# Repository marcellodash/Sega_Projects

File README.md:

# Sega Megadrive_Projects
My Personnal projects for Sega Megadrive

DF_Audio : UART MP3 Player for Sega Megadrive

X-Flash : X-Flash is my Open-Souce alternative to Everdrive

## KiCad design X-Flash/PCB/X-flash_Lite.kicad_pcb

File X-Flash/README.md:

<<<<<<< HEAD
#X-flash

X-Flash is my open-source alternative to Everdrive
**Not finished Yet**
=======
# X-Flash an open source alternative to Everdrive

*Work in Progress*
>>>>>>> 893696249dab5398a9288cfb02d374caec2ab10a

Hardware folder : VHDL file for X-flash CPLD

PCB folder : Kicad + Gerber for the X-flash PCB

Software folder : source code and tools for the BIOS ROM

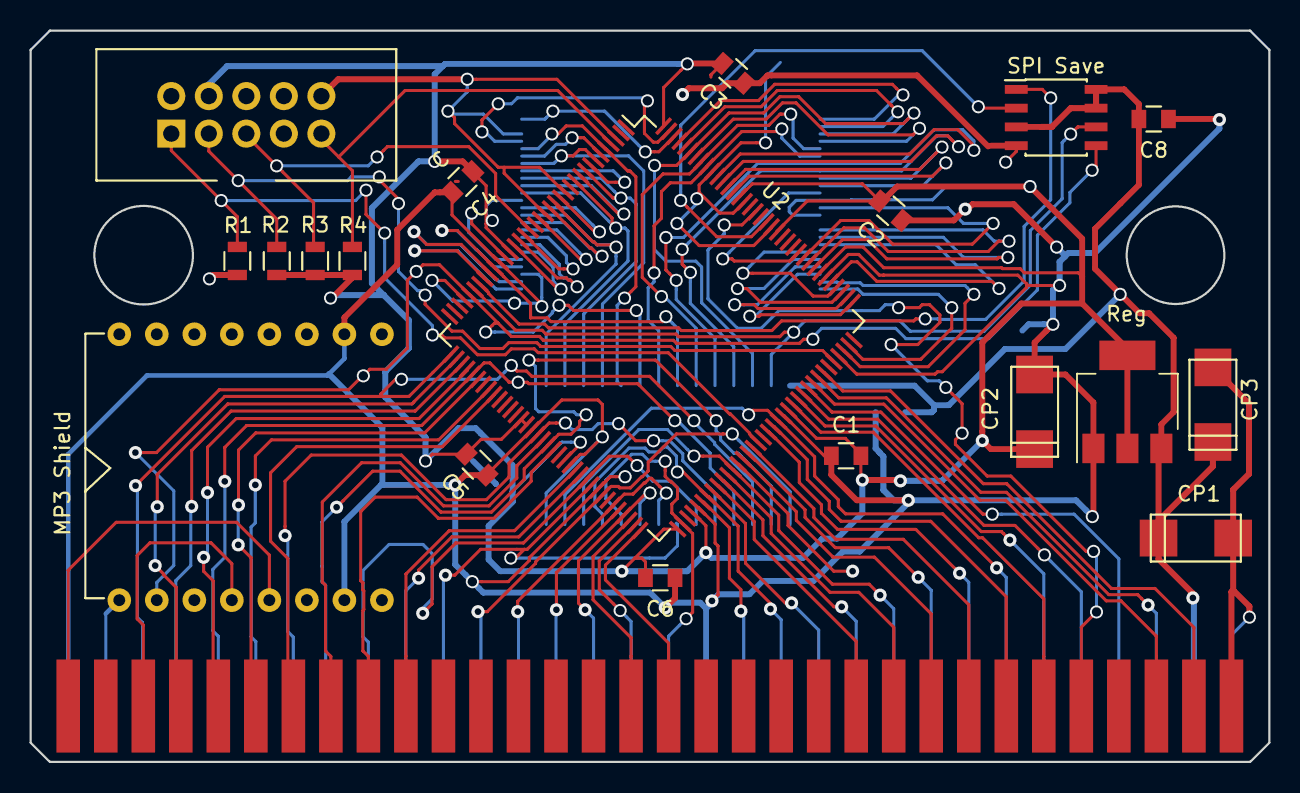
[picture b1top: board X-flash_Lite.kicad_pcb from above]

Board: 2 copper layers, 83.8 x 49.5 mm, 21 parts (0 on the bottom side), 52 nets.

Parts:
C1, C7: C_0805
C2, C3, C4, C5, C6, C8: C; C_0805
CP1: CP1; TantalC_SizeU_EIA-6032
CP2: CP2; TantalC_SizeU_EIA-6032
CP3: CP3; TantalC_SizeU_EIA-6032
J1: 0; AVR-JTAG-ICE
MP3 Shield: DIP-16_W7.62mm
R1, R2, R3, R4: 10K; R_0805
Reg: LM1117-3.3; SOT-223
SPI Save: 25AA512; SOIC-8_3.9x4.9mm_Pitch1.27mm
SST38VF6401: 0; M29W320D
U2: EPM3128ATC144; TQFP-144_20x20mm_Pitch0.5mm

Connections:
/FA0: SST38VF6401.25, U2.29
/FA1: SST38VF6401.24, U2.107
/FA2: SST38VF6401.23, U2.106
/FA3: SST38VF6401.22, U2.109
/FA4: SST38VF6401.21, U2.110
/FA5: SST38VF6401.20, U2.111
/FA6: SST38VF6401.19, U2.112
/FA7: SST38VF6401.18, U2.113
/FA8: SST38VF6401.8, U2.133
/FA9: SST38VF6401.7, U2.134
/FA10: SST38VF6401.6, U2.136
/FA11: SST38VF6401.5, U2.137
/FA12: SST38VF6401.4, U2.138
/FA13: SST38VF6401.3, U2.139
/FA14: SST38VF6401.2, U2.140
/FA15: SST38VF6401.1, U2.141
/FA16: SST38VF6401.48, U2.142
/FA17: SST38VF6401.17, U2.116
/FA18: SST38VF6401.16, U2.117
/FA19: SST38VF6401.9, U2.132
/FA20: SST38VF6401.10, U2.131
/FA21: SST38VF6401.13, U2.118
/FCE: SST38VF6401.26, U2.28
/FD0: SST38VF6401.29, U2.25
/FD1: SST38VF6401.31, U2.22
/FD2: SST38VF6401.33, U2.18
/FD3: SST38VF6401.35, U2.15
/FD4: SST38VF6401.38, U2.11
/FD5: SST38VF6401.40, U2.9
/FD6: SST38VF6401.42, U2.7
/FD7: SST38VF6401.44, U2.5
/FD8: SST38VF6401.30, U2.23
/FD9: SST38VF6401.32, U2.21
/FD10: SST38VF6401.34, U2.16
/FD11: SST38VF6401.36, U2.14
/FD12: SST38VF6401.39, U2.10
/FD13: SST38VF6401.41, U2.8
/FD14: SST38VF6401.43, U2.6
/FD15: SST38VF6401.45, U2.143
/FOE: SST38VF6401.28, U2.27
/FWE: SST38VF6401.11, U2.119
GND: C1.1, C2.1, C3.1, C4.2, C5.1, C6.1, C7.1, C8.1, CP1.2, CP2.2, CP3.2, J1.2, J1.10, MP3 Shield.7, MP3 Shield.10, R1.2, Reg.1, SPI Save.4, SST38VF6401.27, SST38VF6401.46, U2.3, U2.13, U2.17, U2.26, U2.33, U2.52, U2.59, U2.64, U2.77, U2.85, U2.94, U2.105, U2.114, U2.124, U2.129, U2.135
MISO: SPI Save.2, U2.125
MOSI/RX: MP3 Shield.2, SPI Save.5, U2.32
SCLK: SPI Save.6, U2.31
TCK: J1.1, R1.1, U2.89
TDI: J1.9, R4.1, U2.4
TDO: J1.3, R2.1, U2.104
TMS: J1.5, R3.1, U2.20
VCC3: C1.2, C2.2, C3.2, C4.1, C5.2, C6.2, CP2.1, J1.4, R2.2, R3.2, R4.2, Reg.2, Reg.4, SST38VF6401.12, SST38VF6401.14, SST38VF6401.37, U2.24, U2.50, U2.51, U2.58, U2.73, U2.76, U2.95, U2.115, U2.123, U2.130, U2.144
VCC5: C7.2, C8.2, CP1.1, CP3.1, MP3 Shield.1, Reg.3, SPI Save.3, SPI Save.7, SPI Save.8
~CE_SPI: SPI Save.1, U2.30

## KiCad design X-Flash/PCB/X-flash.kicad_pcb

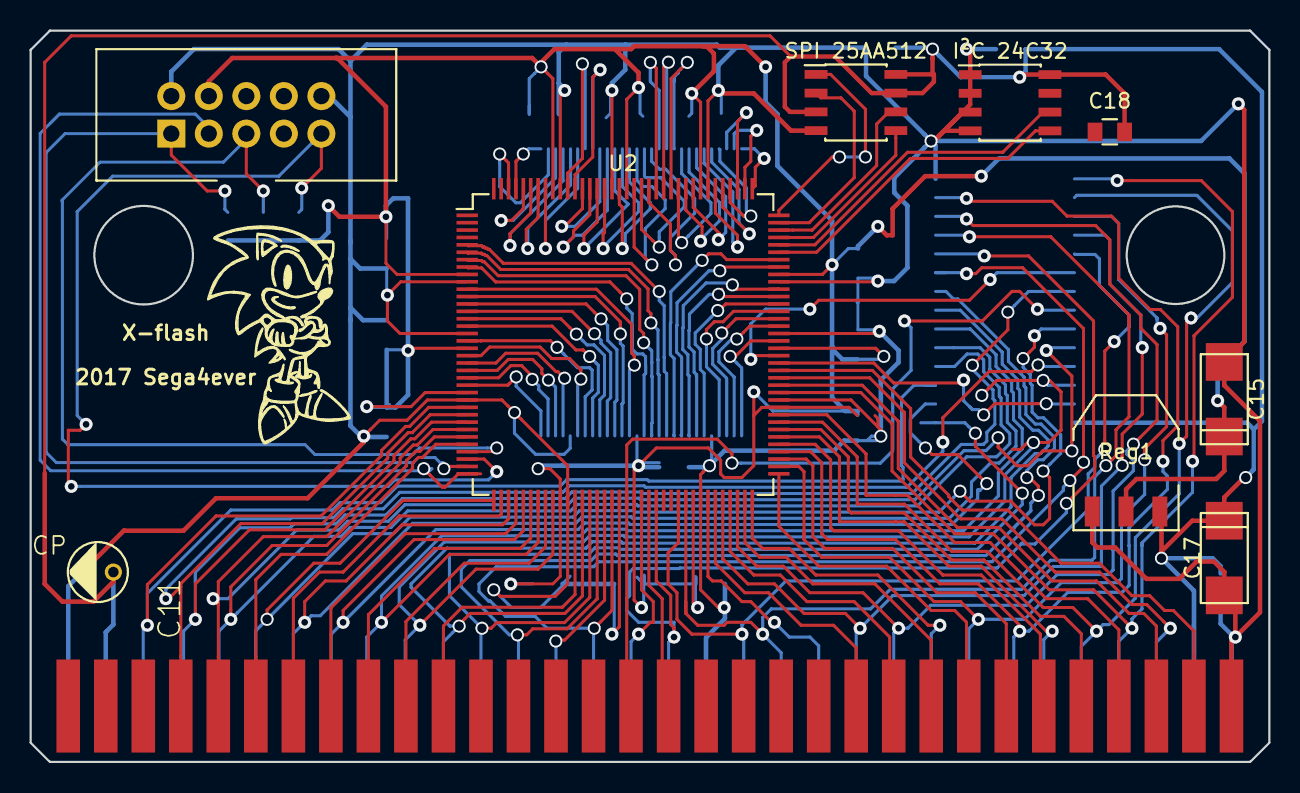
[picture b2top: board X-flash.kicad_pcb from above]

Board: 2 copper layers, 83.8 x 49.5 mm, 28 parts (0 on the bottom side), 62 nets.

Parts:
C1, C2, C3, C4, C5, C6, C7, C8, C9, C10, C12, C13, C14, C16, C18, C19, C20: C; C_0805
C11: CP; E1,8-4
C15, C17: CP; TantalC_SizeU_EIA-6032
IC1: FM1808B-SG; SOIC-28W_7.5x17.9mm_Pitch1.27mm
I²C 24C32: 24C32; SOIC-8_3.9x4.9mm_Pitch1.27mm
J1: 0; AVR-JTAG-ICE
P1: Sega
P2: 0; Sega
Reg1: SOT-223
SPI 25AA512: 25AA512; SOIC-8_3.9x4.9mm_Pitch1.27mm
U2: TQFP-144_20x20mm_Pitch0.5mm

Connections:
/A0: IC1.10, P2.17, U2.59
/A1: IC1.9, P2.15, U2.53
/A2: IC1.8, P2.13, U2.51
/A3: IC1.7, P2.11, U2.49
/A4: IC1.6, P2.9, U2.43
/A5: IC1.5, P2.7, U2.39
/A6: IC1.4, P2.5, U2.31
/A7: IC1.3, P2.3, U2.27
/A8: IC1.25, P1.4, U2.28
/A9: IC1.24, P1.5, U2.30
/A10: IC1.21, P2.4, U2.29
/A11: IC1.23, P2.6, U2.37
/A12: IC1.2, P2.8, U2.41
/A13: IC1.26, P2.10, U2.45
/A14: IC1.1, P2.12, U2.50
/A15: P2.14, U2.52
/A16: P2.16, U2.57
/A17: P1.6, U2.32
/A18: P1.7, U2.38
/A19: P1.8, U2.40
/A20: P1.9, U2.42
/A21: P1.10, U2.44
/A22: P1.11, U2.48
/CE: P1.17, U2.58
/D0: IC1.11, P2.20, U2.63
/D1: IC1.12, P2.23, U2.70
/D2: IC1.13, P2.26, U2.76
/D3: IC1.15, P2.29, U2.84
/D4: IC1.16, P2.28, U2.80
/D5: IC1.17, P2.25, U2.74
/D6: IC1.18, P2.22, U2.68
/D7: IC1.19, P2.19, U2.62
/D8: P2.21, U2.66
/D9: P2.24, U2.72
/D10: P2.27, U2.78
/D11: P2.30, U2.86
/D12: P1.25, U2.73
/D13: P1.24, U2.71
/D14: P1.23, U2.69
/D15: P1.22, U2.67
/OE: IC1.22, P1.16, U2.55
GND: C1.1, C2.2, C3.1, C4.2, C5.2, C6.2, C7.1, C8.1, C9.2, C10.2, C11.-, C12.2, C13.1, C14.2, C15.2, C16.2, C17.2, C19.2, C20.1, IC1.14, I²C 24C32.1, I²C 24C32.2, I²C 24C32.3, I²C 24C32.4, J1.2, J1.10, P1.32, P2.1, P2.18, P2.32, Reg1.1, SPI 25AA512.4, U2.10, U2.17, U2.26, U2.47, U2.54, U2.65, U2.83, U2.92, U2.99, U2.115, U2.128, U2.135
MISO: SPI 25AA512.2, U2.107
MOSI: SPI 25AA512.5, U2.105
SCL: I²C 24C32.6, U2.104
SCLK: SPI 25AA512.6, U2.106
SDA: I²C 24C32.5, U2.103
TCK: J1.1, U2.35
TDI: J1.9, U2.34
TDO: J1.3, U2.36
TMS: J1.5, U2.33
VCC3: C1.2, C2.1, C3.2, C4.1, C5.1, C6.1, C7.2, C8.2, C9.1, C10.1, C12.1, C13.2, C14.1, C15.1, J1.4, Reg1.2, U2.9, U2.19, U2.25, U2.46, U2.56, U2.64, U2.82, U2.90, U2.100, U2.116, U2.126, U2.136
VCC5: C11.+, C16.1, C17.1, C18.2, C19.1, C20.2, IC1.28, I²C 24C32.8, P2.2, P2.31, Reg1.3, SPI 25AA512.3, SPI 25AA512.7, SPI 25AA512.8
~ASEL: P1.26, U2.75
~CE_SPI: SPI 25AA512.1, U2.108
~CE_SRAM: IC1.20, U2.89
~Low_WR: P1.28, U2.79
~MARK3: P1.30, U2.85
~ROM_RST: P1.27, U2.77
~TIME: P1.31, U2.87
~Up_WR: P1.29, U2.81
~WE_SRAM: IC1.27, U2.88

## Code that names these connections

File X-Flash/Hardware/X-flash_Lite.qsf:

# -------------------------------------------------------------------------- #
#
# Copyright (C) 1991-2011 Altera Corporation
# Your use of Altera Corporation's design tools, logic functions 
# and other software and tools, and its AMPP partner logic 
# functions, and any output files from any of the foregoing 
# (including device programming or simulation files), and any 
# associated documentation or information are expressly subject 
# to the terms and conditions of the Altera Program License 
# Subscription Agreement, Altera MegaCore Function License 
# Agreement, or other applicable license agreement, including, 
# without limitation, that your use is for the sole purpose of 
# programming logic devices manufactured by Altera and sold by 
# Altera or its authorized distributors.  Please refer to the 
# applicable agreement for further details.
#
# -------------------------------------------------------------------------- #
#
# Quartus II
# Version 11.0 Build 157 04/27/2011 SJ Full Version
# Date created = 09:53:36  August 19, 2017
#
# -------------------------------------------------------------------------- #
#
# Notes:
#
# 1) The default values for assignments are stored in the file:
#		X-flash_Lite_assignment_defaults.qdf
#    If this file doesn't exist, see file:
#		assignment_defaults.qdf
#
# 2) Altera recommends that you do not modify this file. This
#    file is updated automatically by the Quartus II software
#    and any changes you make may be lost or overwritten.
#
# -------------------------------------------------------------------------- #


set_global_assignment -name FAMILY MAX3000A
set_global_assignment -name DEVICE "EPM3128ATC144-10"
set_global_assignment -name TOP_LEVEL_ENTITY Xflash_Lite
set_global_assignment -name ORIGINAL_QUARTUS_VERSION 11.0
set_global_assignment -name PROJECT_CREATION_TIME_DATE "09:53:36  AUGUST 19, 2017"
set_global_assignment -name LAST_QUARTUS_VERSION 11.0
set_global_assignment -name ERROR_CHECK_FREQUENCY_DIVISOR "-1"
set_global_assignment -name VHDL_FILE "X-flash_Lite.vhd"
set_global_assignment -name OPTIMIZE_HOLD_TIMING OFF
set_global_assignment -name FITTER_EFFORT "STANDARD FIT"
set_global_assignment -name MAX7000_DEVICE_IO_STANDARD "3.3-V LVTTL"
set_location_assignment PIN_5 -to FLASH_DQ[7]
set_location_assignment PIN_6 -to FLASH_DQ[14]
set_location_assignment PIN_7 -to FLASH_DQ[6]
set_location_assignment PIN_8 -to FLASH_DQ[13]
set_location_assignment PIN_10 -to FLASH_DQ[12]
set_location_assignment PIN_9 -to FLASH_DQ[5]
set_location_assignment PIN_11 -to FLASH_DQ[4]
set_location_assignment PIN_14 -to FLASH_DQ[11]
set_location_assignment PIN_15 -to FLASH_DQ[3]
set_location_assignment PIN_16 -to FLASH_DQ[10]
set_location_assignment PIN_18 -to FLASH_DQ[2]
set_location_assignment PIN_21 -to FLASH_DQ[9]
set_location_assignment PIN_22 -to FLASH_DQ[1]
set_location_assignment PIN_23 -to FLASH_DQ[8]
set_location_assignment PIN_25 -to FLASH_DQ[0]
set_location_assignment PIN_27 -to OE_FLASH
set_location_assignment PIN_28 -to CE_FLASH
set_location_assignment PIN_29 -to FLASH_ADDR[0]
set_location_assignment PIN_143 -to FLASH_DQ[15]
set_location_assignment PIN_30 -to CE_SPI
set_location_assignment PIN_31 -to SCLK
set_location_assignment PIN_37 -to MD_ADDR[7]
set_location_assignment PIN_38 -to MD_ADDR[8]
set_location_assignment PIN_39 -to MD_ADDR[10]
set_location_assignment PIN_40 -to MD_ADDR[9]
set_location_assignment PIN_41 -to MD_ADDR[6]
set_location_assignment PIN_42 -to MD_ADDR[17]
set_location_assignment PIN_44 -to MD_ADDR[11]
set_location_assignment PIN_45 -to MD_ADDR[18]
set_location_assignment PIN_53 -to MD_ADDR[5]
set_location_assignment PIN_54 -to MD_ADDR[19]
set_location_assignment PIN_55 -to MD_ADDR[12]
set_location_assignment PIN_56 -to MD_ADDR[20]
set_location_assignment PIN_63 -to MD_ADDR[3]
set_location_assignment PIN_60 -to MD_ADDR[21]
set_location_assignment PIN_61 -to MD_ADDR[13]
set_location_assignment PIN_65 -to MD_ADDR[14]
set_location_assignment PIN_67 -to MD_ADDR[2]
set_location_assignment PIN_68 -to MD_ADDR[15]
set_location_assignment PIN_69 -to MD_ADDR[1]
set_location_assignment PIN_70 -to MD_OE
set_location_assignment PIN_71 -to MD_ADDR[16]
set_location_assignment PIN_72 -to MD_CE
set_location_assignment PIN_74 -to MD_ADDR[0]
set_location_assignment PIN_78 -to MD_DQ[7]
set_location_assignment PIN_79 -to MD_DQ[0]
set_location_assignment PIN_84 -to MD_DQ[1]
set_location_assignment PIN_86 -to MD_DQ[13]
set_location_assignment PIN_87 -to MD_DQ[9]
set_location_assignment PIN_88 -to MD_DQ[12]
set_location_assignment PIN_91 -to MD_DQ[5]
set_location_assignment PIN_92 -to ASEL
set_location_assignment PIN_93 -to MD_DQ[2]
set_location_assignment PIN_96 -to SOFT_RST
set_location_assignment PIN_97 -to MD_DQ[10]
set_location_assignment PIN_98 -to MD_DQ[4]
set_location_assignment PIN_99 -to MD_DQ[3]
set_location_assignment PIN_100 -to Mark3
set_location_assignment PIN_101 -to MD_DQ[11]
set_location_assignment PIN_102 -to TIMEE
set_location_assignment PIN_4 -to TDI
set_location_assignment PIN_20 -to TMS
set_location_assignment PIN_104 -to TDO
set_location_assignment PIN_89 -to TCK
set_location_assignment PIN_106 -to FLASH_ADDR[2]
set_location_assignment PIN_107 -to FLASH_ADDR[1]
set_location_assignment PIN_109 -to FLASH_ADDR[3]
set_location_assignment PIN_110 -to FLASH_ADDR[4]
set_location_assignment PIN_111 -to FLASH_ADDR[5]
set_location_assignment PIN_112 -to FLASH_ADDR[6]
set_location_assignment PIN_113 -to FLASH_ADDR[7]
set_location_assignment PIN_116 -to FLASH_ADDR[17]
set_location_assignment PIN_117 -to FLASH_ADDR[18]
set_location_assignment PIN_118 -to FLASH_ADDR[21]
set_location_assignment PIN_119 -to FLASH_WE
set_location_assignment PIN_125 -to MISO
set_location_assignment PIN_131 -to FLASH_ADDR[20]
set_location_assignment PIN_132 -to FLASH_ADDR[19]
set_location_assignment PIN_133 -to FLASH_ADDR[8]
set_location_assignment PIN_134 -to FLASH_ADDR[9]
set_location_assignment PIN_136 -to FLASH_ADDR[10]
set_location_assignment PIN_137 -to FLASH_ADDR[11]
set_location_assignment PIN_138 -to FLASH_ADDR[12]
set_location_assignment PIN_139 -to FLASH_ADDR[13]
set_location_assignment PIN_140 -to FLASH_ADDR[14]
set_location_assignment PIN_141 -to FLASH_ADDR[15]
set_location_assignment PIN_142 -to FLASH_ADDR[16]
set_location_assignment PIN_127 -to LWR
set_location_assignment PIN_81 -to MD_DQ[15]
set_location_assignment PIN_83 -to MD_DQ[14]
set_location_assignment PIN_80 -to MD_DQ[8]
set_location_assignment PIN_82 -to MD_DQ[6]
set_location_assignment PIN_62 -to MD_ADDR[4]
set_location_assignment PIN_32 -to TX
set_global_assignment -name MISC_FILE "C:/Users/I3-2100/Documents/CPLD/EPM3128/X-flash_Lite/X-flash_Lite.dpf"

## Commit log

2017-06-10 add MP3 Demo
2017-11-12 Add X-flash Project
2017-12-30 Preliminary FatFs Support
2018-05-11 Add bankswitch support
2018-05-12 Upgrade Bankswitch
2018-05-13 Full Bankswitch support
2018-05-15 Preliminary SPI Support
